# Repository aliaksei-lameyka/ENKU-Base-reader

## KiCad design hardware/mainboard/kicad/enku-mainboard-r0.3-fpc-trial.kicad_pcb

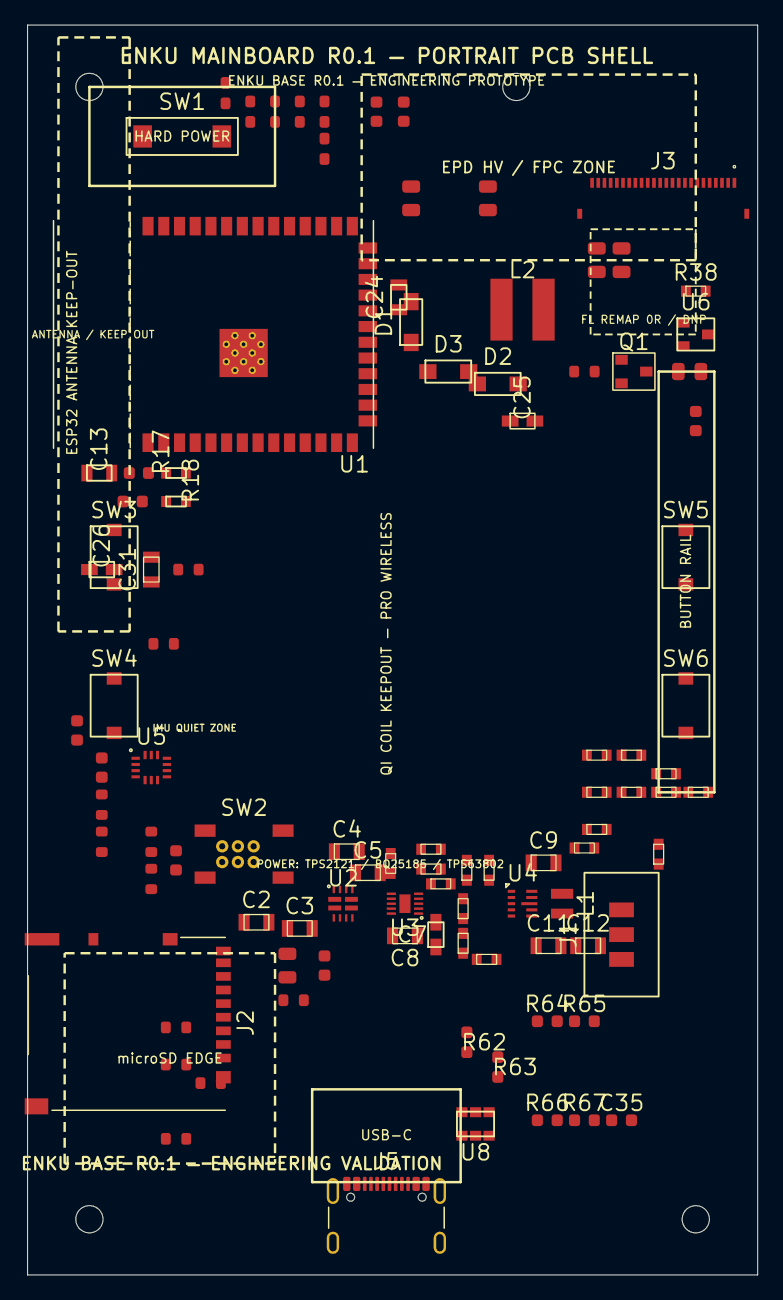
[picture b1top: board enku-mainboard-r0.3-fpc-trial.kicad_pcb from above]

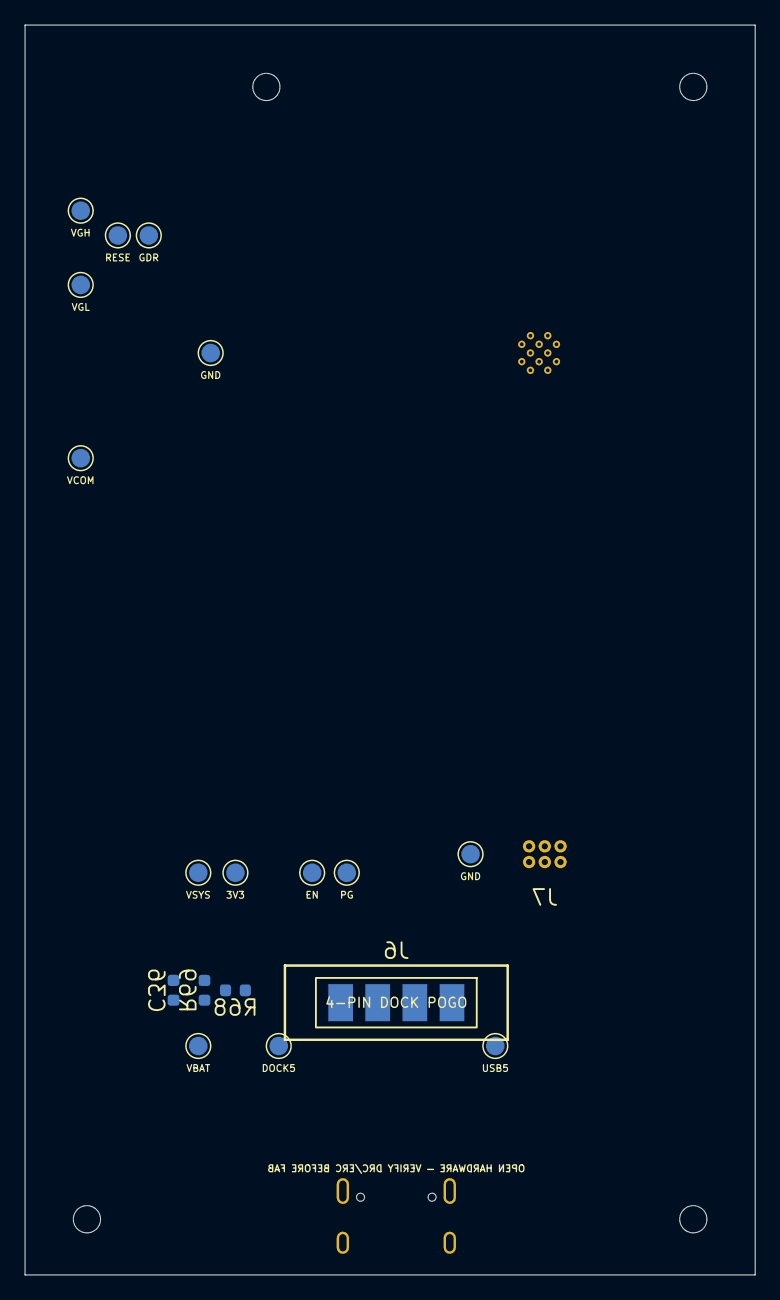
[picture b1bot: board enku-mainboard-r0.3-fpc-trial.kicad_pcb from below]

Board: 4 copper layers, 59.0 x 101.0 mm, 122 parts (19 on the bottom side), 76 nets, no tracks yet.

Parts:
C1, C10, C14, C17, C18, C19, C20, C21: 100nF; C_0603_1608Metric
C2, C3, C4, C9, C13, C16: 10uF 10V; C_0805_2012Metric
C5, C24, C25, C26, C27, C28, C29, C31: 4.7uF 25V; C_0805_2012Metric
C6: 100nF 25V; C_0603_1608Metric
C7: 10uF 25V; C_0805_2012Metric
C8: 4.7uF 10V; C_0805_2012Metric
C11, C12: 22uF 10V; C_0805_2012Metric
C15: 1uF; C_0603_1608Metric
C22, C23: 1uF 25V; C_0603_1608Metric
C30: 1uF 25V X7R; C_0805_2012Metric
C35: 4.7nF; C_0603_1608Metric
C36: 10nF; C_0603_1608Metric
D1, D2, D3: MBR0530; D_SOD-123
H1, H2, H3, H4: MountingHole_2.2mm_M2
J1: 1S LiPo + NTC; JST_PH_3_PLACEMENT
J2: Hirose DM3AT-SF-PEJM5; MICROSD_DM3AT_ENKU
J3: FH34SRJ-24S-0.5SH(50); FH34SRJ-24S-0.5SH
J5: GCT USB4105-GF-A-120; USB_C_Receptacle_GCT_USB4105-xx-A_16P_TopMnt_Horizontal
J6: 4-pin pogo dock; DOCK_POGO_4
J7: Tag-Connect TC2030-IDC-NL; Tag-Connect_TC2030-IDC-NL_2x03_P1.27mm_Vertical
L1: 0.47uH DFE201612E-R47M=P2; Murata_DFE201612E
L2: 10uH TYS5040100M-10; TYS5040_5x5
Q1: IRLML6346TRPBF; SOT-23
R1: 100k 1%; R_0603_1608Metric
R2, R3, R4, R5: 0R STRAP; R_0603_1608Metric
R6, R7, R19, R28, R29: 0R; R_0603_1608Metric
R8: 18k 1%; R_0603_1608Metric
R9: 1k 1%; R_0603_1608Metric
R10, R13, R16, R35, R36, R69: 100k; R_0603_1608Metric
R11, R17, R18, R68: 10k; R_0603_1608Metric
R12: 10k DNP; R_0603_1608Metric
R14: 511k 1%; R_0603_1608Metric
R15: 91k 1%; R_0603_1608Metric
R20, R21, R22, R64, R65: 0R (22R tune); R_0603_1608Metric
R23: 47k; R_0603_1608Metric
R24, R25: 4.7k; R_0603_1608Metric
R26: 2M 1%; R_0603_1608Metric
R27: 680k 1%; R_0603_1608Metric
R30, R31, R32, R33, R34: 22R; R_0603_1608Metric
R37: 2.2R 1% 0805; R_0805_2012Metric
R38: 1M 1%; R_0603_1608Metric
R62, R63: 5.1k 1%; R_0603_1608Metric
R66: 1M; R_0603_1608Metric
R67: 0R DNP; R_0603_1608Metric
SW1: HARD POWER; HARD_POWER_SWITCH_PLACEMENT
SW2: BOOT / RECOVERY; SW_SPST_TL3342
SW3: BTN_L1; READING_BUTTON_PLACEMENT
SW4: BTN_L2; READING_BUTTON_PLACEMENT
SW5: BTN_R1; READING_BUTTON_PLACEMENT
SW6: BTN_R2; READING_BUTTON_PLACEMENT
TP1, TP14: GND; TestPoint_Pad_D1.5mm
TP2: VBUS_USB; TestPoint_Pad_D1.5mm
TP3: VBUS_DOCK; TestPoint_Pad_D1.5mm
TP4: VBAT; TestPoint_Pad_D1.5mm
TP5: VSYS; TestPoint_Pad_D1.5mm
TP6: 3V3_SYS; TestPoint_Pad_D1.5mm
TP7: SYS_EN; TestPoint_Pad_D1.5mm
TP8: REG_PG; TestPoint_Pad_D1.5mm
TP9: EPD_GDR; TestPoint_Pad_D1.5mm
TP10: EPD_RESE; TestPoint_Pad_D1.5mm
TP11: EPD_VGH; TestPoint_Pad_D1.5mm
TP12: EPD_VGL; TestPoint_Pad_D1.5mm
TP13: EPD_VCOM; TestPoint_Pad_D1.5mm
U1: ESP32-S3-WROOM-1-N16R8; ESP32-S3-WROOM-1
U2: TPS2121; TPS2121_RUX0012A
U3: BQ25185DLHR; BQ25185_DLH0010A
U4: TPS63802DLAR; TPS63802_DLA0010A
U5: BMI270; BMI270_Bosch_LGA14
U6: DRV5032FBDBZR; SOT-23
U8: USBLC6-2SC6; SOT-23-6

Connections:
3V3_SYS: C11.1, C12.1, C13.1, C14.1, C16.1, C17.1, C18.1, C19.1, C20.1, J2.4, J3.15, J7.1, R11.1, R12.1, R14.1, R16.1, R17.1, R18.1, R23.1, R24.1, R25.1, R28.1, R35.1, R36.1, TP6.1, U1.2, U4.6, U5.5, U5.8, U5.12, U6.1
BAT_ADC: C21.1, R26.2, R27.1, U1.39
BAT_TS: J1.3, U3.6
BOOT: J7.5, R18.2, SW2.1, U1.27
BTN_L1: SW3.1, U1.4
BTN_L2: SW4.1, U1.5
BTN_R1: SW5.1, U1.6
BTN_R2: SW6.1, U1.7
CHG_CE_N: R10.1, U3.4
CHG_ILIM_VSET: R8.1, U3.7
CHG_ISET: R9.1, U3.8
CHG_STAT1: R11.2, U1.8, U3.9
CHG_STAT2: R12.2, U3.3
DOCK_DETECT: C36.1, R68.2, R69.1, U1.38
DOCK_DETECT_RAW: J6.3, R68.1
EPD_BS1: J3.8, R29.1
EPD_BUSY: J3.9, U1.25
EPD_CP_NEG: C25.2, D2.2, D3.1
EPD_CS: R32.1, U1.22
EPD_CS_PANEL: J3.12, R32.2, R35.2
EPD_DC: R31.1, U1.23
EPD_DC_PANEL: J3.11, R31.2
EPD_GDR: J3.2, Q1.1, R38.1, TP9.1
EPD_MOSI_PANEL: J3.14, R34.2
EPD_RESE: J3.3, Q1.2, R37.1, TP10.1
EPD_RST: R30.1, U1.24
EPD_RST_PANEL: J3.10, R30.2, R36.2
EPD_SCLK_PANEL: J3.13, R33.2
EPD_SW: C25.1, D1.2, L2.2, Q1.3
EPD_VCI: C22.1, C31.1, J3.16, L2.1, R28.2
EPD_VCOM: C30.1, J3.24, TP13.1
EPD_VDD: C23.1, J3.18
EPD_VGH: C24.1, D1.1, J3.21, TP11.1
EPD_VGL: C26.1, D3.2, J3.23, TP12.1
EPD_VSH1: C27.1, J3.20
EPD_VSH2: C28.1, J3.5
EPD_VSL: C29.1, J3.22
ESP_EN: C15.1, J7.6, R17.2, U1.3
GND: C1.2, C2.2, C3.2, C4.2, C5.2, C6.2, C7.2, C8.2, C9.2, C10.2, C11.2, C12.2, C13.2, C14.2, C15.2, C16.2, C17.2, C18.2, C19.2, C20.2, C21.2, C22.2, C23.2, C24.2, C26.2, C27.2, C28.2, C29.2, C30.2, C31.2, C35.2, C36.2, D2.1, J1.2, J2.6, J3.17, J3.S1, J3.S2, J5.A1, J5.A12, J5.B1, J5.B12, J6.1, J6.4, J7.2, R1.2, R3.2, R5.2, R6.2, R7.2, R8.2, R9.2, R10.2, R13.2, R15.2, R27.2, R29.2, R37.2, R38.2, R62.2, R63.2, R66.2, R67.2, R69.2, SW2.2, SW3.2, SW4.2, SW5.2, SW6.2, TP1.1, TP14.1, U1.1, U1.40, U1.41, U2.12, U3.5, U3.11, U4.2, U4.3, U4.8, U5.1, U5.6, U5.7, U6.3, U8.2
HALL_INT: U1.10, U6.2
I2C_SCL: R25.2, U1.17, U5.13
I2C_SDA: R24.2, U1.12, U5.14
IMU_INT1: U1.11, U5.4
MUX_CP2: R4.2, R5.1, U2.3
MUX_ILIM: R1.1, U2.10
MUX_OV1: R6.1, U2.5
MUX_OV2: R7.1, U2.4
MUX_PR1: R2.2, R3.1, U2.6
MUX_SS: C1.1, U2.11
REG_FB: R14.2, R15.1, U4.4
REG_L1: L1.1, U4.9
REG_L2: L1.2, U4.7
REG_PG: R16.2, TP8.1, U4.5
SD_CS: R19.1, U1.18
SD_CS_CARD: J2.2, R19.2, R23.2
SD_MISO_CARD: J2.7, R22.1
SD_MOSI_CARD: J2.3, R20.2
SD_SCLK_CARD: J2.5, R21.2
SPI_MISO: R22.2, U1.21
SPI_MOSI: R20.1, R34.1, U1.19
SPI_SCLK: R21.1, R33.1, U1.20
SYS_EN: R13.1, SW1.2, TP7.1, U4.1
UART_RX: J7.4, U1.36
UART_TX: J7.3, U1.37
USB_CC1: J5.A5, R62.1
USB_CC2: J5.B5, R63.1
USB_DM: R65.2, U1.13
USB_DM_CONN: J5.A7, J5.B7, R65.1, U8.3, U8.4
USB_DP: R64.2, U1.14
USB_DP_CONN: J5.A6, J5.B6, R64.1, U8.1, U8.6
USB_SHIELD: C35.1, J5.S, R66.1, R67.1
VBAT: C8.1, J1.1, R26.1, TP4.1, U3.2
VBUS_DOCK: C3.1, J6.2, R4.1, TP3.1, U2.2
VBUS_EXT: C4.1, C5.1, C6.1, U2.1, U2.8, U3.10
VBUS_USB: C2.1, J5.A4, J5.A9, J5.B4, J5.B9, R2.1, TP2.1, U2.7, U8.5
VSYS: C7.1, C9.1, C10.1, SW1.1, TP5.1, U3.1, U4.10

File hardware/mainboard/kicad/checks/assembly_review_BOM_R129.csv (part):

Reference,Value,Manufacturer,MPN,Assembly,Footprint,Side,BoardX_mm,BoardY_mm,NativeCPL_X_mm,NativeCPL_Y_mm,Rotation_deg,MPN_field_status
C10,100nF,Yageo,CC0603KRX7R9BB104,FIT,ENKU:C_CC0603_YAGEO_REFLOW_TRANSFER,front,63.0,86.5,63.0,-86.5,0.0,EXPLICIT
C11,22uF 10V,Yageo,CC0805MKX5R6BB226,FIT,ENKU:C_CC0805_YAGEO_REFLOW_TRANSFER,front,60.1,94.4,60.1,-94.4,0.0,EXPLICIT
C12,22uF 10V,Yageo,CC0805MKX5R6BB226,FIT,ENKU:C_CC0805_YAGEO_REFLOW_TRANSFER,front,63.125,94.4,63.125,-94.4,0.0,EXPLICIT
C13,10uF 10V,Yageo,CC0805KKX5R6BB106,FIT,ENKU:C_CC0805_YAGEO_REFLOW_TRANSFER,front,30.0,59.0,30.0,-59.0,0.0,EXPLICIT
C14,100nF,Yageo,CC0603KRX7R9BB104,FIT,ENKU:C_CC0603_YAGEO_REFLOW_TRANSFER,front,30.0,56.0,30.0,-56.0,0.0,EXPLICIT
C15,1uF,Yageo,CC0603KRX7R8BB105,FIT,ENKU:C_CC0603_YAGEO_REFLOW_TRANSFER,front,34.0,58.0,34.0,-58.0,0.0,EXPLICIT
C16,10uF 10V,Yageo,CC0805KKX5R6BB106,FIT,ENKU:C_CC0805_YAGEO_REFLOW_TRANSFER,front,39.0,96.0,39.0,-96.0,90.0,EXPLICIT
C17,100nF,Yageo,CC0603KRX7R9BB104,FIT,ENKU:C_CC0603_YAGEO_REFLOW_TRANSFER,front,42.0,96.0,42.0,-96.0,90.0,EXPLICIT
C18,100nF,Yageo,CC0603KRX7R9BB104,FIT,ENKU:C_CC0603_YAGEO_REFLOW_TRANSFER,front,22.0,77.4,22.0,-77.4,90.0,EXPLICIT
C19,100nF,Yageo,CC0603KRX7R9BB104,FIT,ENKU:C_CC0603_YAGEO_REFLOW_TRANSFER,front,24.0,80.0,24.0,-80.0,90.0,EXPLICIT
C2,1uF 10V,Yageo,CC0805KKX7R6BB105,FIT,ENKU:C_CC0805_YAGEO_REFLOW_TRANSFER,front,36.5,91.85,36.5,-91.85,0.0,EXPLICIT
C21,100nF,Yageo,CC0603KRX7R9BB104,FIT,ENKU:C_CC0603_YAGEO_REFLOW_TRANSFER,front,30.0,87.5,30.0,-87.5,90.0,EXPLICIT
C22,1uF 25V,Yageo,CC0603KRX7R8BB105,FIT,ENKU:C_CC0603_YAGEO_REFLOW_TRANSFER,front,46.2,27.0,46.2,-27.0,90.0,EXPLICIT
C23,1uF 25V,Yageo,CC0603KRX7R8BB105,FIT,ENKU:C_CC0603_YAGEO_REFLOW_TRANSFER,front,48.4,27.0,48.4,-27.0,90.0,EXPLICIT
C24,4.7uF 25V,Yageo,CC0805KKX7R8BB475,FIT,ENKU:C_CC0805_YAGEO_REFLOW_TRANSFER,front,47.3,42.0,47.3,-42.0,90.0,EXPLICIT
C25,4.7uF 25V,Yageo,CC0805KKX7R8BB475,FIT,ENKU:C_CC0805_YAGEO_REFLOW_TRANSFER,front,58.0,52.0,58.0,-52.0,0.0,EXPLICIT
C26,4.7uF 25V,Yageo,CC0805KKX7R8BB475,FIT,ENKU:C_CC0805_YAGEO_REFLOW_TRANSFER,front,52.5,45.5,52.5,-45.5,90.0,EXPLICIT
C27,4.7uF 25V,Yageo,CC0805KKX7R8BB475,FIT,ENKU:C_CC0805_YAGEO_REFLOW_TRANSFER,front,49.0,34.0,49.0,-34.0,90.0,EXPLICIT
C28,4.7uF 25V,Yageo,CC0805KKX7R8BB475,FIT,ENKU:C_CC0805_YAGEO_REFLOW_TRANSFER,front,73.12,28.5,73.12,-28.5,90.0,EXPLICIT
C29,4.7uF 25V,Yageo,CC0805KKX7R8BB475,FIT,ENKU:C_CC0805_YAGEO_REFLOW_TRANSFER,front,64.0,39.0,64.0,-39.0,90.0,EXPLICIT
C30,1uF 25V X7R,Yageo,CC0805KKX7R8BB105,FIT,ENKU:C_CC0805_YAGEO_REFLOW_TRANSFER,front,66.0,39.0,66.0,-39.0,90.0,EXPLICIT
C31,4.7uF 25V,Yageo,CC0805KKX7R8BB475,FIT,ENKU:C_CC0805_YAGEO_REFLOW_TRANSFER,front,53.0,43.0,53.0,-43.0,180.0,EXPLICIT
C35,4.7nF,Yageo,CC0603KRX7R9BB472,FIT,ENKU:C_CC0603_YAGEO_REFLOW_TRANSFER,front,66.0,108.5,66.0,-108.5,0.0,EXPLICIT
C37,100nF 10V,Yageo,CC0603KRX7R9BB104,FIT,ENKU:C_CC0603_YAGEO_REFLOW_TRANSFER,front,38.5,67.0,38.5,-67.0,0.0,EXPLICIT
C38,100nF 10V,Yageo,CC0603KRX7R9BB104,FIT,ENKU:C_CC0603_YAGEO_REFLOW_TRANSFER,front,60.0,65.0,60.0,-65.0,0.0,EXPLICIT
C39,1nF C0G 10V,Yageo,CC0603JRNPO9BN102,FIT,ENKU:C_CC0603_YAGEO_REFLOW_TRANSFER,front,66.0,76.0,66.0,-76.0,0.0,EXPLICIT
C4,1uF 25V,Yageo,CC0805KKX7R8BB105,FIT,ENKU:C_CC0805_YAGEO_REFLOW_TRANSFER,front,43.8,86.8,43.8,-86.8,0.0,EXPLICIT
C5,4.7uF 25V,Yageo,CC0805KKX7R8BB475,FIT,ENKU:C_CC0805_YAGEO_REFLOW_TRANSFER,front,45.5,88.5,45.5,-88.5,0.0,EXPLICIT
C6,100nF 25V,Yageo,CC0603KRX7R9BB104,FIT,ENKU:C_CC0603_YAGEO_REFLOW_TRANSFER,front,45.5,93.0,45.5,-93.0,0.0,EXPLICIT
C7,10uF 25V,Yageo,CC0805KKX5R8BB106,FIT,ENKU:C_CC0805_YAGEO_REFLOW_TRANSFER,front,51.6,93.5,51.6,-93.5,90.0,EXPLICIT
C8,4.7uF 10V,Yageo,CC0805KKX5R6BB475,FIT,ENKU:C_CC0805_YAGEO_REFLOW_TRANSFER,front,48.5,93.6,48.5,-93.6,180.0,EXPLICIT
C9,10uF 10V,Yageo,CC0805KKX5R6BB106,FIT,ENKU:C_CC0805_YAGEO_REFLOW_TRANSFER,front,59.7,87.7,59.7,-87.7,0.0,EXPLICIT
D1,MBR0530T1G,onsemi,MBR0530T1G,FIT,ENKU:MBR0530T1G_ONSEMI_CASE425H,front,49.25,44.0,49.25,-44.0,-90.0,EXPLICIT
D2,MBR0530T1G,onsemi,MBR0530T1G,FIT,ENKU:MBR0530T1G_ONSEMI_CASE425H,front,56.0,50.0,56.0,-50.0,180.0,EXPLICIT
D3,MBR0530T1G,onsemi,MBR0530T1G,FIT,ENKU:MBR0530T1G_ONSEMI_CASE425H,front,52.0,48.0,52.0,-48.0,180.0,EXPLICIT
H1,,,,BARE_PCB,ENKU:MOUNT_HOLE_D2_2_BOARD_ONLY,front,29.0,22.5,,,0.0,NOT_AN_ASSEMBLED_PART
H2,,,,BARE_PCB,ENKU:MOUNT_HOLE_D2_2_BOARD_ONLY,front,57.5,25.0,,,0.0,NOT_AN_ASSEMBLED_PART
H3,,,,BARE_PCB,ENKU:MOUNT_HOLE_D2_2_BOARD_ONLY,front,23.0,116.5,,,0.0,NOT_AN_ASSEMBLED_PART
H4,,,,BARE_PCB,ENKU:MOUNT_HOLE_D2_2_BOARD_ONLY,front,72.0,116.5,,,0.0,NOT_AN_ASSEMBLED_PART
J1,1S LiPo + NTC,,,FIT,ENKU:JST_PH_S3B-PH-SM4-TB_1x03-1MP_P2.00mm_Horizontal,front,69.8,93.5,69.8,-93.5,90.0,FIELD_FREEZE_PENDING
J2,Hirose DM3AT-SF-PEJM5,,,FIT,ENKU:MICROSD_DM3AT_ENKU,front,27.0,100.7,27.0,-100.7,-90.0,FIELD_FREEZE_PENDING
J3,FH34SRJ-24S-0.5SH(50),Hirose,FH34SRJ-24S-0.5SH(50),FIT,ENKU:FH34SRJ-24S-0.5SH,front,69.27,34.0,69.27,-34.0,0.0,EXPLICIT
J5,GCT USB4105-GF-A-120,,,FIT,ENKU:USB4105_EXISTING_LANDS_SHIELD_S,front,47.0,117.325,47.0,-117.325,0.0,FIELD_FREEZE_PENDING
J7,Tag-Connect TC2030-IDC-NL,,,BARE_PCB,ENKU:TC2030_NL_CONTACTS_PIN1,back,35.0,87.0,,,0.0,NOT_AN_ASSEMBLED_PART
L1,0.47uH DFE201612E-R47M=P2,,,FIT,ENKU:Murata_DFE201612E,front,61.2,91.0,61.2,-91.0,-90.0,FIELD_FREEZE_PENDING
L2,47uH TYS5040470M-10,,,FIT,ENKU:TYS5040_5x5,front,58.0,43.0,58.0,-43.0,0.0,FIELD_FREEZE_PENDING
Q1,IRLML6346TRPBF,,,FIT,ENKU:IRLML6346_INFINEON_MICRO3,front,67.0,48.0,67.0,-48.0,0.0,FIELD_FREEZE_PENDING
Q2,AO3401A,,,FIT,ENKU:AO3401A_AOS_SOT23,front,55.5,82.5,55.5,-82.5,0.0,FIELD_FREEZE_PENDING
R10,100k,Yageo,RC0603FR-07100KL,FIT,ENKU:R_RC0603_YAGEO_REFLOW,front,51.8,89.4,51.8,-89.4,0.0,EXPLICIT
R11,10k,Yageo,RC0603FR-0710KL,FIT,ENKU:R_RC0603_YAGEO_REFLOW,front,53.2,91.4,53.2,-91.4,90.0,EXPLICIT
R12,10k DNP,Yageo,RC0603FR-0710KL,DNP,ENKU:R_RC0603_YAGEO_REFLOW,front,53.3,94.2,,,90.0,EXPLICIT
R13,100k,Yageo,RC0603FR-07100KL,FIT,ENKU:R_RC0603_YAGEO_REFLOW,front,69.0,85.3,69.0,-85.3,90.0,EXPLICIT
R14,511k 1%,Yageo,RC0603FR-07511KL,FIT,ENKU:R_RC0603_YAGEO_REFLOW,front,55.3,88.3,55.3,-88.3,90.0,EXPLICIT
R15,91k 1%,Yageo,RC0603FR-0791KL,FIT,ENKU:R_RC0603_YAGEO_REFLOW,front,53.9,88.3,53.9,-88.3,90.0,EXPLICIT
R16,100k,Yageo,RC0603FR-07100KL,FIT,ENKU:R_RC0603_YAGEO_REFLOW,front,55.45,95.5,55.45,-95.5,0.0,EXPLICIT
R17,10k,Yageo,RC0603FR-0710KL,FIT,ENKU:R_RC0603_YAGEO_REFLOW,front,34.0,56.0,34.0,-56.0,0.0,EXPLICIT
R18,10k,Yageo,RC0603FR-0710KL,FIT,ENKU:R_RC0603_YAGEO_REFLOW,front,34.0,61.0,34.0,-61.0,0.0,EXPLICIT
R19,0R,Yageo,RC0603JR-070RL,FIT,ENKU:R_RC0603_YAGEO_REFLOW,front,38.0,101.0,38.0,-101.0,0.0,EXPLICIT
R20,0R (22R tune),Yageo,RC0603JR-070RL,FIT,ENKU:R_RC0603_YAGEO_REFLOW,front,38.0,104.0,38.0,-104.0,0.0,EXPLICIT
R21,0R (22R tune),Yageo,RC0603JR-070RL,FIT,ENKU:R_RC0603_YAGEO_REFLOW,front,38.0,107.0,38.0,-107.0,0.0,EXPLICIT
R22,0R (22R tune),Yageo,RC0603JR-070RL,FIT,ENKU:R_RC0603_YAGEO_REFLOW,front,30.0,110.0,30.0,-110.0,0.0,EXPLICIT
R23,47k,Yageo,RC0603FR-0747KL,FIT,ENKU:R_RC0603_YAGEO_REFLOW,front,39.5,98.8,39.5,-98.8,0.0,EXPLICIT
R24,4.7k,Yageo,RC0603FR-074K7L,FIT,ENKU:R_RC0603_YAGEO_REFLOW,front,26.0,76.5,26.0,-76.5,90.0,EXPLICIT
R25,4.7k,Yageo,RC0603FR-074K7L,FIT,ENKU:R_RC0603_YAGEO_REFLOW,front,26.0,73.0,26.0,-73.0,90.0,EXPLICIT
R26,2M 1%,Yageo,RC0603FR-072ML,FIT,ENKU:R_RC0603_YAGEO_REFLOW,front,28.0,86.0,28.0,-86.0,90.0,EXPLICIT
R27,680k 1%,Yageo,RC0603FR-07680KL,FIT,ENKU:R_RC0603_YAGEO_REFLOW,front,28.0,89.0,28.0,-89.0,90.0,EXPLICIT
R28,0R,Yageo,RC0603JR-070RL,FIT,ENKU:R_RC0603_YAGEO_REFLOW,front,63.0,48.0,63.0,-48.0,0.0,EXPLICIT
R29,0R,Yageo,RC0603JR-070RL,FIT,ENKU:R_RC0603_YAGEO_REFLOW,front,42.0,30.0,42.0,-30.0,90.0,EXPLICIT
R30,22R,Yageo,RC0603FR-0722RL,FIT,ENKU:R_RC0603_YAGEO_REFLOW,front,42.0,27.0,42.0,-27.0,90.0,EXPLICIT
R31,22R,Yageo,RC0603FR-0722RL,FIT,ENKU:R_RC0603_YAGEO_REFLOW,front,40.0,27.0,40.0,-27.0,90.0,EXPLICIT
R32,22R,Yageo,RC0603FR-0722RL,FIT,ENKU:R_RC0603_YAGEO_REFLOW,front,38.0,27.0,38.0,-27.0,90.0,EXPLICIT
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
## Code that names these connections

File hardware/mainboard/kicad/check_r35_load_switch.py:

#!/usr/bin/env python3
"""R35 high-side PMOS local switch, battery measurement gate, GoodDisplay 24-pin release block."""
import argparse
import re
from pathlib import Path
HERE=Path(__file__).parent
PCB=(HERE/"enku-mainboard-r1.2-base-local-load-switch.kicad_pcb").read_text()
SCH=(HERE/"power.kicad_sch").read_text()
EPD=(HERE/"epd_hv.kicad_sch").read_text()
def balanced(src,start):
    depth=0; quoted=False; escaped=False
    for i in range(start,len(src)):
        c=src[i]
        if quoted:
            if escaped: escaped=False
            elif c=="\\": escaped=True
            elif c=='"': quoted=False
        elif c=='"': quoted=True
        elif c=='(': depth+=1
        elif c==')':
            depth-=1
            if depth==0:return src[start:i+1]
    raise ValueError("Unbalanced footprint")
def fp(ref):
    p=PCB.index('(property "Reference" "'+ref+'"')
    return balanced(PCB,PCB.rfind("(footprint ",0,p))
def pad(ref,num):
    lines=[l for l in fp(ref).splitlines() if '(pad "'+str(num)+'" ' in l]
    assert len(lines)==1,(ref,num,len(lines))
    m=re.search(r'\(net \d+ "([^"]+)"\)',lines[0])
    return m[1] if m else "NC"
def main():
    cli=argparse.ArgumentParser()
    cli.add_argument("--release",action="store_true")
    args=cli.parse_args()
    assert PCB.count('(footprint "')==125
    assert not re.search(r'(?m)^  \((segment|via|zone)\b',PCB)
    nets={("SW1","1"):"PWR_GATE",("SW1","2"):"GND",
          ("U4","1"):"SYS_EN",("U4","10"):"SYS_EN",
          ("C9","1"):"SYS_EN",("C9","2"):"GND",
          ("C10","1"):"SYS_EN",("C10","2"):"GND",
          ("R13","1"):"SYS_EN",("R13","2"):"GND",
          ("Q2","1"):"PWR_GATE",("Q2","2"):"VSYS",("Q2","3"):"SYS_EN",
          ("R40","1"):"VSYS",("R40","2"):"PWR_GATE",
          ("U3","1"):"VSYS",("TP5","1"):"VSYS",("TP7","1"):"SYS_EN",
          ("R26","1"):"BAT_ADC_SW",("R26","2"):"BAT_ADC",
          ("R27","1"):"BAT_ADC",("R27","2"):"GND",
          ("U9","1"):"BAT_ADC_SW",("U9","2"):"VBAT",("U9","3"):"GND",("U9","4"):"3V3_SYS",("U9","5"):"VBAT",
          ("C37","1"):"VBAT",("C37","2"):"GND",("R39","1"):"3V3_SYS",("R39","2"):"GND"}
    for (ref,num),expected in nets.items():
        assert pad(ref,num)==expected,(ref,num,pad(ref,num),expected)
    assert '(global_label "PWR_GATE" (shape input) (at 196.85 127 0)' in SCH
    assert '(global_label "GND" (shape output) (at 213.36 127 180)' in SCH
    assert '(property "Reference" "Q2"' in SCH and '(property "Reference" "R40"' in SCH
    assert '(property "Value" "AO3401A"' in fp("Q2")
    assert '(pad "1" smd rect (at -1 -0.95)' in fp("Q2"),"AO3401A physically marked pin1 must be GATE"
    assert '(pad "2" smd rect (at -1 0.95)' in fp("Q2"),"AO3401A physically pin2 must be SOURCE"
    assert '(fp_circle (center -1.38 -1.47)' in fp("Q2")
    for coord in ("187.96 57.15","243.84 62.23","243.84 85.09"):
        assert f'(global_label "SYS_EN" (shape input) (at {coord} 0)' in SCH,coord
    pins={1:"NC",2:"EPD_GDR",3:"EPD_RESE",4:"NC",5:"EPD_VSH2",
          6:"NC",7:"NC",8:"EPD_BS1",9:"EPD_BUSY",10:"EPD_RST_PANEL",
          11:"EPD_DC_PANEL",12:"EPD_CS_PANEL",13:"EPD_SCLK_PANEL",
          14:"EPD_MOSI_PANEL",15:"3V3_SYS",16:"EPD_VCI",17:"GND",
          18:"EPD_VDD",19:"NC",20:"EPD_VSH1",21:"EPD_VGH",
          22:"EPD_VSL",23:"EPD_VGL",24:"EPD_VCOM"}
    for num,expected in pins.items():
        assert pad("J3",str(num))==expected,(num,pad("J3",str(num)),expected)
    assert pad("R28","1")=="3V3_SYS" and pad("R28","2")=="EPD_VCI"
    assert '(property "Value" "0R"' in fp("R28")
    r28=balanced(EPD,EPD.index('(symbol (lib_id "ENKU:R") (at 190.5 44.45'))
    assert '(dnp no)' in r28
    print("R35 POWER/ADC/EPD PASS: 125 physical footprints; SW1 controls PMOS gate only; Q2 source VSYS/drain switched SYS_EN; J3-24pin and U9 isolated ADC gate locked.")
    print("RELEASE BLOCKED: unmeasured TMUX1101 off leakage and reverse injection, switch MPN/current, charger STAT backfeed, J3 pin5 VDHR/VSH2 contradiction, 3D FPC and off-state bench.")
    if args.release:raise SystemExit("FAB BLOCKED: physical electrical signoff required")
if __name__=="__main__":main()

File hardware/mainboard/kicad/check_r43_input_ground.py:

#!/usr/bin/env python3
"""R43 four reading-button GND-plane fanouts: robust source-level constraints.

Native KiCad re-fill + complete ERC/priority DRC is the actual electrical authority.
The case-edge switch footprint remains provisional; these are pilot paths only.
"""
import re
from check_r43_assembly import PCB,footprints,pads
fps=footprints()
pp=pads(fps)
assert len(fps)==132
tracks=re.findall(r'(?m)^  \(segment \(start ([-\d.]+) ([-\d.]+)\) \(end ([-\d.]+) ([-\d.]+)\) \(width ([-\d.]+)\) \(layer "([^"]+)"\) \(net (\d+)\)',PCB)
vias=re.findall(r'(?m)^  \(via \(at ([-\d.]+) ([-\d.]+)\) \(size ([-\d.]+)\) \(drill ([-\d.]+)\) \(layers "([^"]+)" "([^"]+)"\) \(net (\d+)\)',PCB)
assert len(tracks)==442,len(tracks)
assert len(vias)==121,len(vias)
assert len(re.findall(r'(?m)^  \(zone \(net 1\) \(net_name "GND"\)',PCB))==2
for ref,x,y,vx,vy in [
 ("SW3",25,65.2,28,67),("SW4",25,77.2,28,77.2),
 ("SW5",71.2,65.2,68,65.2),("SW6",71.2,77.2,68,77.2)
]:
    pad=[p for p in pp if p[0]==ref and p[1]=="2"]
    assert len(pad)==1,(ref,pad)
    assert pad[0][3]=="GND",(ref,pad)
    xmin,ymin,xmax,ymax=pad[0][4]
    assert xmin<=x<=xmax and ymin<=y<=ymax,ref
    assert any(float(a)==x and float(b)==y and float(c)==vx and float(d)==vy and layer=="F.Cu" and n=="1" for a,b,c,d,w,layer,n in tracks),ref
    assert any(float(a)==vx and float(b)==vy and size=="0.70" and drill=="0.30" and net=="1" for a,b,size,drill,l1,l2,net in vias),ref
    assert 27+0.7<vx<69-0.7,(ref,"pilot GND via outside two native-filled reference zones")
for a,b,c,d in [(25,65.2,25,64),(25,77.2,22,76.225),(25,77.2,24,79.225)]:
    assert any(float(x)==a and float(y)==b and float(u)==c and float(v)==d and lay=="F.Cu" and n=="1" for x,y,u,v,w,lay,n in tracks)
for ref,pin,net in [('C26','2','GND'),('C18','2','GND'),('C19','2','GND'),('SW3','1','BTN_L1'),('SW4','1','BTN_L2'),('SW5','1','BTN_R1'),('SW6','1','BTN_R2')]:
    assert any(p[0]==ref and p[1]==pin and p[3]==net for p in pp),(ref,pin,net)
assert not any(t[-1] in ('48','49','50','51') for t in tracks), "Do not imply physical switch signal path: real side-button MPN still TBD"
assert not any(t[-1] in ('6','7','57','58') for t in tracks),"USB D+/D- pair must remain unrouted until PCBWay stackup qualification"
print("R43 FOUR BUTTON GND SOURCE PASS: SW3..SW6 pad2 to inner GND via, near C26/C18/C19 ground joined, 132 footprints, 442 tracks, 121 vias.")
print("RELEASE HOLD: SW3..SW6 provisional mechanical land patterns not production-footprint approved, side-button GPIO nets, PWR_GATE SW1 and USB differential pair still need routing.")
